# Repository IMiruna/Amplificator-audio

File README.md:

# Amplificator-audio

La acest proiect din timpul facultatii am lucrat impreuna cu alte 2 persoane pentru a realiza un amplificator audio. Amplificatorul cuprinde doua tranzistoare, de tipul NPN si PNP, fiind astfel un amplificator de clasa B. Fiecare transiztor conduce doar jumatate din timp, iar in cealalta jumatate este blocat, nu conduce curent electric si prin urmare puterea disipata sub forma de caldura este nula. Pe langa acestia, am integrat si condensatoare de diferite capacitati, rezistente, diode Schotkky, potentiometre si un amplificator operational de tip TL072CP.

Am realizat intai schema si placa de circuit in programele LTSpice si KiCad (pozele 1 si 2), dupa care am construit amplificatorul efectiv, montand fiecare piesa pe rand, pe placa. La final, pentru testarea functionarii, am conectat amplificatorul la o sursa de tensiune externa si la o boxa (pozele 3, 4, 5, 6).

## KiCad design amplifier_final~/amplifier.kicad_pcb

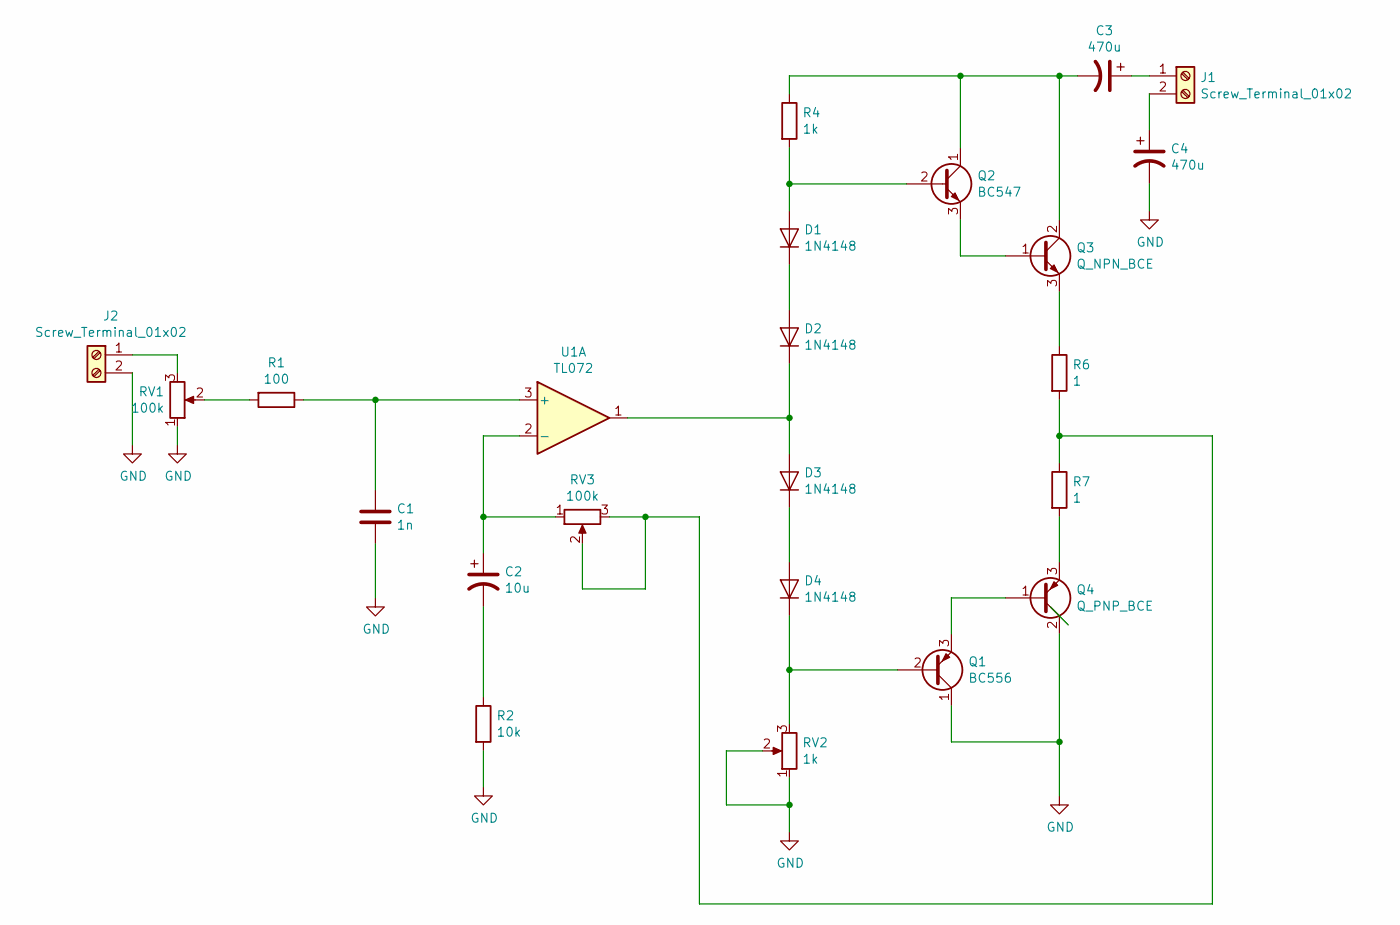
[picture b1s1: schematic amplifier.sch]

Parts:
C1: 1n; CP_Radial_D6.3mm_P2.50mm
C2: 10u; CP_Radial_D6.3mm_P2.50mm
C3, C4: 470u; CP_Radial_D8.0mm_P5.00mm
D1, D2, D3, D4: 1N4148; D_DO-35_SOD27_P7.62mm_Horizontal
J1, J2: Screw_Terminal_01x02; TerminalBlock_bornier-2_P5.08mm
Q1: BC556; TO-92_Inline
Q2: BC547; TO-92_Inline
Q3: Q_NPN_BCE; TO-220-3_Vertical
Q4: Q_PNP_BCE; TO-220-3_Vertical
R1: 100; R_Axial_DIN0204_L3.6mm_D1.6mm_P5.08mm_Horizontal
R2: 10k; R_Axial_DIN0204_L3.6mm_D1.6mm_P5.08mm_Horizontal
R4: 1k; R_Axial_DIN0204_L3.6mm_D1.6mm_P5.08mm_Horizontal
R6, R7: 1; R_Axial_DIN0204_L3.6mm_D1.6mm_P5.08mm_Horizontal
RV1, RV3: 100k; Potentiometer_Bourns_3006P_Horizontal
RV2: 1k; Potentiometer_Bourns_3006P_Horizontal
U1: TL072; DIP-8_W7.62mm

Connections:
GND: C1.2, C4.2, J2.2, Q1.1 (C), Q4.2 (C), R2.2, RV1.1, RV2.1, RV2.2
unnamed: C1.1, R1.1, U1.3 (+)
unnamed: C2.1, RV3.1, U1.2 (-)
unnamed: C2.2, R2.1
unnamed: C3.1, J1.1
unnamed: C3.2, Q2.1 (C), Q3.2 (C), R4.1
unnamed: C4.1, J1.2
unnamed: D1.1 (K), D2.2 (A)
unnamed: D1.2 (A), Q2.2 (B), R4.2
unnamed: D2.1 (K), D3.2 (A), U1.1
unnamed: D3.1 (K), D4.2 (A)
unnamed: D4.1 (K), Q1.2 (B), RV2.3
unnamed: J2.1, RV1.3
unnamed: Q1.3 (E), Q4.1 (B)
unnamed: Q2.3 (E), Q3.1 (B)
unnamed: Q3.3 (E), R6.1
unnamed: Q4.3 (E), R7.2
unnamed: R1.2, RV1.2
unnamed: R6.2, R7.1, RV3.2, RV3.3

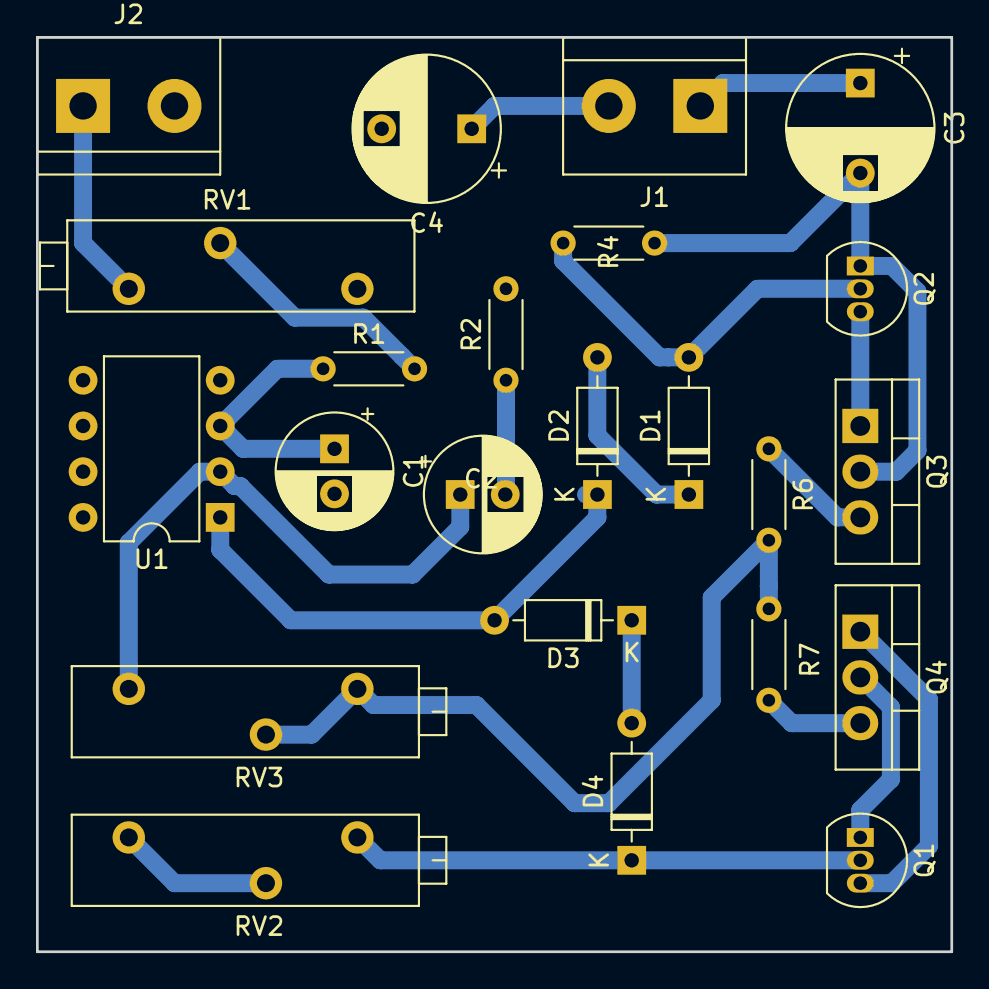
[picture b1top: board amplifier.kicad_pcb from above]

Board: 2 copper layers, 50.8 x 50.8 mm, 23 parts (0 on the bottom side), 19 nets.
